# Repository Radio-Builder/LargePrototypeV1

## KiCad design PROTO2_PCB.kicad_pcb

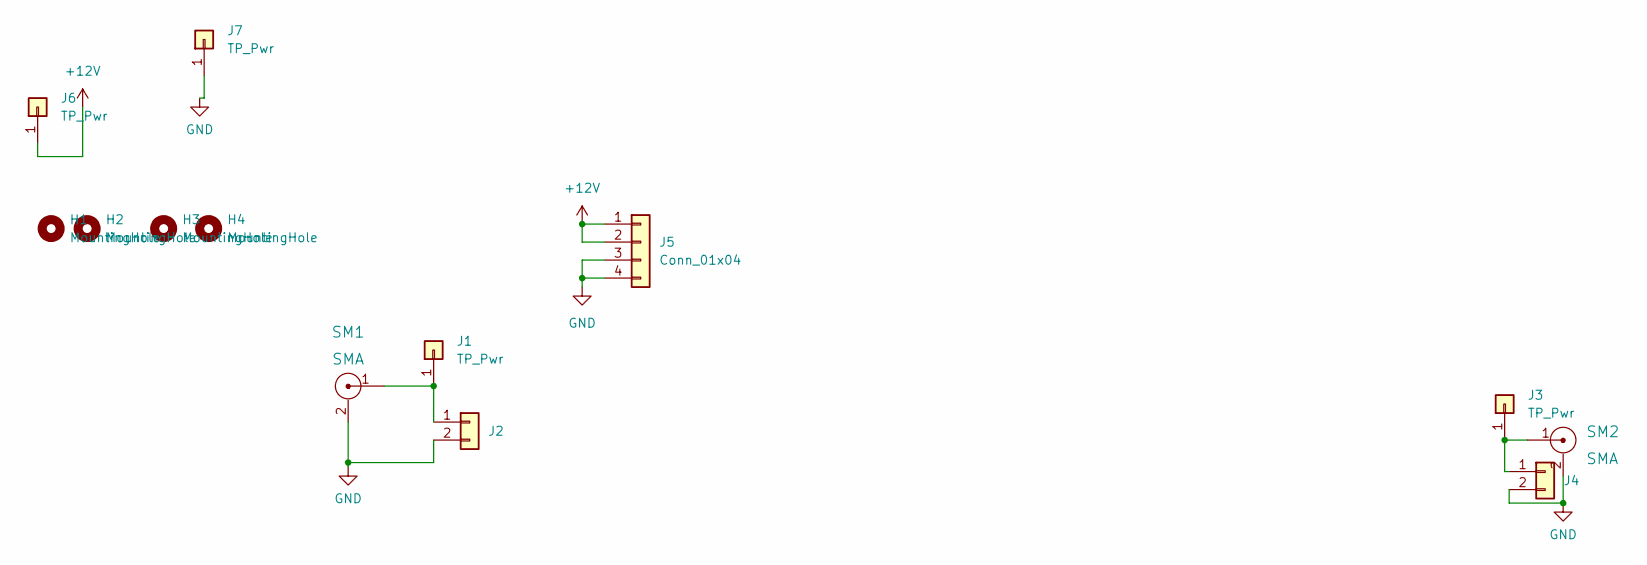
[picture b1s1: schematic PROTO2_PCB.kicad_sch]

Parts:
H1, H2, H3, H4: MountingHole; TestPoint_Plated_Hole_D3.0mm
J1, J3, J6, J7: TP_Pwr; PinHeader_1x01_P2.54mm_Vertical
J2, J4: Conn_01x02; PinHeader_1x02_P2.54mm_Vertical
J5: Conn_01x04; PinSocket_1x04_P2.54mm_Vertical
SM1, SM2: SMA

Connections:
+12V: J5.1, J5.2, J6.1
GND: J2.2, J4.2, J5.3, J5.4, J7.1, SM1.2, SM2.2
unnamed: J1.1, J2.1, SM1.1
unnamed: J3.1, J4.1, SM2.1

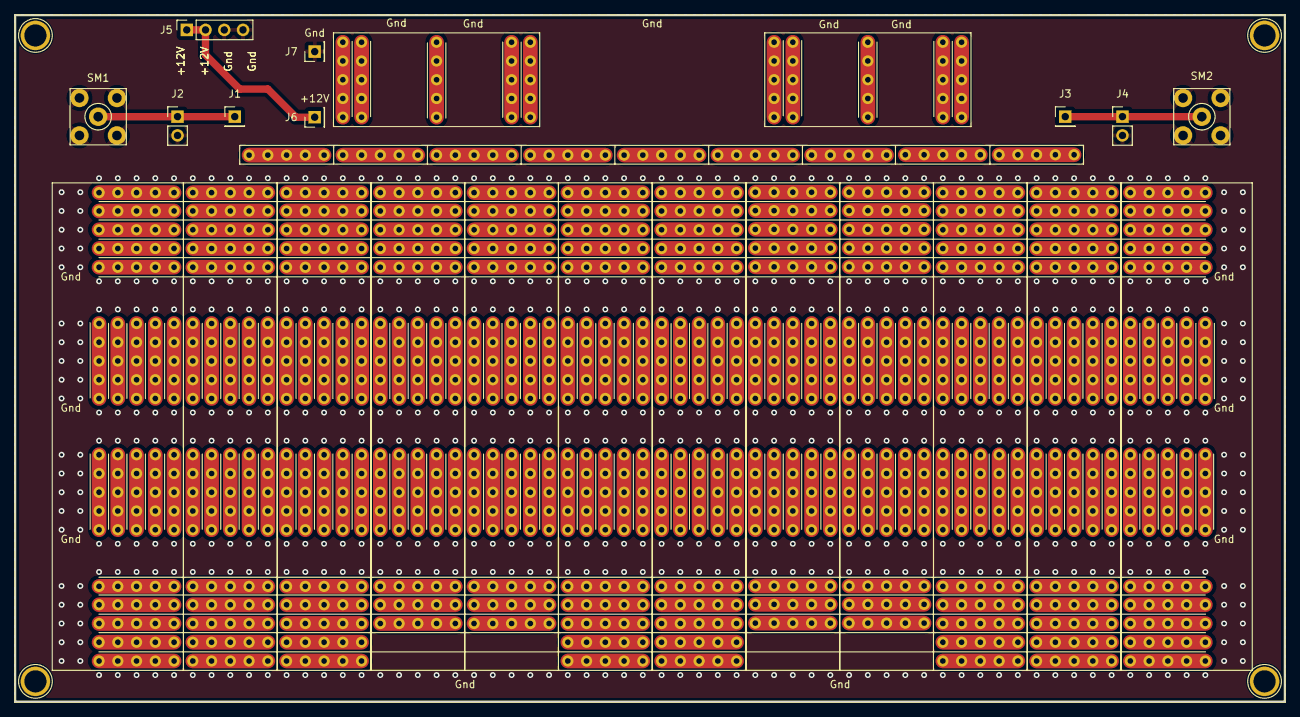
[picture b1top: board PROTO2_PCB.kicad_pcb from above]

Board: 2 copper layers, 172.0 x 93.0 mm, 13 parts (0 on the bottom side), 4 nets.
